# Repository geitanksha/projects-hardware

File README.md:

# projects-hardware

A collection combining all the projects worked on related to all things hardware.

Projects worked on:

- Superheterodyne Am Radio Receiver: Created a functional Superheterodyne AM Receiver that would extract a modulated signal and demodulate it, complete with components as mentioned: Preselect Band-Pass Filter, IF Amplifier, Envelope Detector, Audio Amplifier and Loudspeaker.
  Skills Employed: Capacitor Circuit Analysis, Filter analysis, Modulation and Demodulation Properties, Circuit Analysis.
- WECE Smart Glasses: Worked on by RSO Women in ECE at the University of Illinois at Urbana-Champaign, crafting glasses that would provide basic information at eye-level via reflection off of sunglasses.
  Skills Employed: Flutter App Development, ESP-32 Board (Bluetooth / charging facilities), OLED Display, Circuit Design
- Virtual Gloves: Team of 4 created a glove that would use flexing ability of the finger and force tough generated by fingertips to input a letter / character, replacing the need for a keyboard. Completed prototype that generated binary (1 finger with 2 flexes / forces generated)
  Skills Employed: Arduino Uno, Flex Sensors, Force Sensing Resistors, Python
- ECE 110: DC Motor Control PWM: For the final project, constructed a circuit that would use the resistive ratios of a PWM signal to run the car in a stright line, and then built a car-lock system using a wheatstone bridge that would only let current flow if a specific resistor was used.

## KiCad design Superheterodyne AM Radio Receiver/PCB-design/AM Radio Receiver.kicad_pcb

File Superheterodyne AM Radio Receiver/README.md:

# Superheterodyne AM Radio Receiver

We had to construct a Superheterodyne AM Radio Receiver which would take the modulated input signal, and perform modifications so it could be listened to via an Audio-jack compatible speaker.

Overall Circuit:

PCB Design Result:

Component 1: Envelope Detector:

Component 2: System Amplifier:

Component 3: Band Pass Filter:

PCB Other Angles:

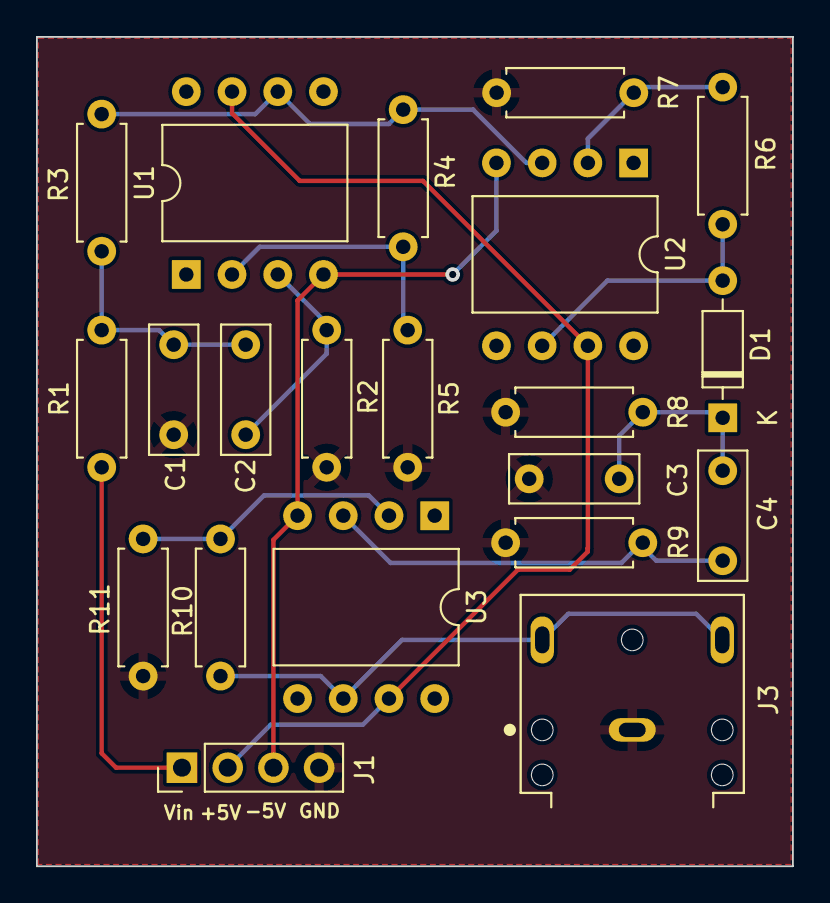
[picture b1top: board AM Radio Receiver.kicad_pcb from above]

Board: 2 copper layers, 42.0 x 46.1 mm, 21 parts (0 on the bottom side), 14 nets.

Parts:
C1, C2: .01µ; C_Disc_D7.0mm_W2.5mm_P5.00mm
C3: 0.1µ; C_Disc_D7.0mm_W2.5mm_P5.00mm
C4: 33µ; C_Disc_D7.0mm_W2.5mm_P5.00mm
D1: D; D_DO-35_SOD27_P7.62mm_Horizontal
J1: Conn_01x04_Male; PinHeader_1x04_P2.54mm_Vertical
J3: SJ1-3523N; CUI_SJ1-3523N
R1: 5k; R_Axial_DIN0207_L6.3mm_D2.5mm_P7.62mm_Horizontal
R2: 1.6k; R_Axial_DIN0207_L6.3mm_D2.5mm_P7.62mm_Horizontal
R3: 1k; R_Axial_DIN0207_L6.3mm_D2.5mm_P7.62mm_Horizontal
R4, R5: 3.3k; R_Axial_DIN0207_L6.3mm_D2.5mm_P7.62mm_Horizontal
R6, R7, R10, R11: R; R_Axial_DIN0207_L6.3mm_D2.5mm_P7.62mm_Horizontal
R8: 2k; R_Axial_DIN0207_L6.3mm_D2.5mm_P7.62mm_Horizontal
R9: 10k; R_Axial_DIN0207_L6.3mm_D2.5mm_P7.62mm_Horizontal
U1, U2, U3: LM741; DIP-8_W10.16mm

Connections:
+5V: J1.2, U1.7 (V+), U2.7 (V+), U3.7 (V+)
-5V: J1.3, U1.4 (V-), U2.4 (V-), U3.4 (V-)
GND: C1.2, C3.1, J1.4, J3.1, R2.1, R5.2, R7.2, R8.2, R9.2, R11.2
unnamed: C1.1, C2.1, R1.2, R3.2
unnamed: C2.2, R2.2, U1.3 (+)
unnamed: C3.2, C4.2, D1.1 (K), R8.1
unnamed: C4.1, R9.1, U3.3 (+)
unnamed: D1.2 (A), R6.1, U2.6
unnamed: J3.2, J3.3, R10.1, U3.6
unnamed: R3.1, R4.1, U1.6, U2.3 (+)
unnamed: R4.2, R5.1, U1.2 (-)
unnamed: R6.2, R7.1, U2.2 (-)
unnamed: R10.2, R11.1, U3.2 (-)
v_in: J1.1, R1.1

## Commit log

2022-08-05 README for hardware projects
2022-08-05 DC Motor Files committed
2022-08-05 Updating ECE 385 Lab reports
2022-08-05 Rubik's Cube Simulator files
2022-08-05 Committing README for Rubik's Cube
2022-08-05 Committing AM Radio Receiver files
2022-08-05 Virtual Gloves files committed
2022-08-05 Updating AM Radio Receiver README
2022-08-05 REAMDE for virtual Gloves
2022-08-05 updating hardware projects readme
2022-08-07 Logic processor report
2022-08-07 logic processor code
    contains all components described in the readme
2022-08-07 Lab 3 readme
2022-08-07 16 bit adders report committed
2022-08-07 README for 16-bit adders
2022-08-07 multiplier readme created
2022-08-08 adders labs systemverilog files uploaded
2023-03-24 update main readme
2023-03-24 update dc motor readme
2023-03-24 uploading lab reports for car and lock system
2023-03-24 updating the radio receiver readme
2023-03-24 committing the pcb design for radio
2023-03-24 updating location of pcb design for radio receiver
2023-03-24 updating readme for virtual gloves
2023-03-24 arduino code for the project
2023-03-24 code for 3 finger sensors
2023-03-24 lab reports for virtual gloves
